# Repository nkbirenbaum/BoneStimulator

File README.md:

# bone-stimulator
Bone stimulator project w/ Saad Javeed

## PCB versions

+ bone_stim_v0  
  + Original constant bone stimulator circuit created by electronics shop  
  + Much larger and not designed to be implantable  
  + Potentiometer allowed for adjustment of stimulation current  
+ bone_stim_v1  
  + Nathan's edit of v0 circuit that makes circuit smaller and stimulation constant  
  + Used by Jawad Khalifeh in trial studies  
+ bone_stim_pulsed_v2  
  + Nathan's redesign for Saad Javeed based on literature ([Cho et al 2018](https://doi.org/10.1016/j.spinee.2018.12.011))  
  + Incorporates stimulator circuit controlled by ATTINY for pulsed stimulation  
  + Did not work on initial testing 4/12 and needed to be resized anyway (printed square from expressPCB)  
+ bone_stim_pulsed_v3  
  + Redesigned to have round edges and an incorporated schematic file  
  + Described below and should be used in future runs  

## Software versions

- Note: software versions do not correlate with PCB versions  
- bone_stim_v1  
  - Uses delay and delayMicroseconds (delay is not very accurate)  
- bone_stim_v2  
  - Uses if(millis() - time_now_ms > PULSE_PERIOD_MS) condition with time_now_ms as unsigned long  
- bone_stim_v3  
  - WORK IN PROGRESS  
  - Need to add button push and blinking funcitonality  
  - Need to sleep in between pulses  
  - Measure current draw if possible  

## Paper

+ "Effect of the type of electrical stimulation on spinal fusion in a rat posterolateral spinal fusion model" Pyung Goo Cho, MD, Gyu Yeol Ji, PhD, Yoon Ha, PhD, Hye Yeong Lee, Dong Ah Shin, MD, PhD. December 22, 2018 DOI: https://doi.org/10.1016/j.spinee.2018.12.011  
+ Link: [The Spine Journal](https://www.thespinejournalonline.com/article/S1529-9430(18)31320-2/fulltext)  
+   

# PCB design

- bone_stim_pulsed_v3 finalized by NKB 04/14/2022.  
- Gerber and drill files for ordering boards are available in the "bone_stim_pulsed_v3" folder.  

<sup>bone stim pulsed v3 PCB </sup>  

<sup>bone stim pulsed v3 schematic</sup>  

## Parts, datasheets, and schematics

+ Microcontroller
  + ATTINY13-10SSU ([DigiKey](https://www.digikey.com/en/products/detail/microchip-technology/ATTINY13V-10SSU/1008458) / [datasheet](https://ww1.microchip.com/downloads/en/DeviceDoc/2535S.pdf))  
  + ATTINY programming clip ([Amazon](https://www.amazon.com/Pomona-Electronics-5250-Plated-Spacing/dp/B00JJ4G13I/ref=sr_1_3?keywords=soic8+clip&qid=1645148900&sr=8-3))  
  + ATTINY pinout  

- Current source
  - LM334 ([DigiKey](https://www.digikey.com/en/products/detail/texas-instruments/LM334M/3701392) / [datasheet](https://www.ti.com/general/docs/suppproductinfo.tsp?distId=10&gotoUrl=https%3A%2F%2Fwww.ti.com%2Flit%2Fgpn%2Flm134))  

+ Pushbutton
  + EVQ-3PLA15 ([Digikey](https://www.digikey.com/en/products/detail/panasonic-electronic-components/EVQ-3PLA15/7561411?s=N4IgTCBcDaIAoEYxgCwGYBsBhAKgWgDkAREAXQF8g) / [datasheet](https://www3.panasonic.biz/ac/e_download/control/switch/light-touch/catalog/sw_lt_eng_49s.pdf))  

- LED
  - LS P476-Q1R2-1-0-20-R18-Z ([Digikey](https://www.digikey.com/en/products/detail/osram-opto-semiconductors-inc/LS-P476-Q1R2-1-0-20-R18-Z/7325513?s=N4IgjCBcoMxgnFUBjKAzAhgGwM4FMAaEAeygG1wYAmABhoHYQiBWADnpkaIDYwxmYTENyphuAFiFj2VKlKrUaiImAXjmzecwXd54kV3BVu8cYJUwaYeroC6RAA4AXKCADKTgE4BLAHYBzEABfFjMkEFRITFxCEnIQDmYJKTMaJKlWcRpuViFaOhMhHNYYcwSONKFMtLLTZnpJFTpLQXsQZ1cPHwDgnkzwyOj8IlJICjBqnJA2jsh3Lz9AkPBmOgH0bGG4sfAEbKE2VSKaBSL%2BZWFRC4l9IXolCCJ6MBO7-ho3jTuqcUfy56qNF%2BVVY%2BxmLjmXUWvRAAFo5NAIlAvABXWKjCiaWxBZYIig4AC2ABMAARYPCkzwUknTHjhbxE1ywl5-WYgIROACeDjwrgwOFQOKAA) / [datasheet](https://dammedia.osram.info/media/resource/hires/osram-dam-2493611/LS%20P476.pdf))  

+ Battery
  + CR-2450/H1AN ([Digikey](https://www.digikey.com/en/products/detail/panasonic-bsg/CR-2450-H1AN/2404067?s=N4IgTCBcDaIMYCcC0YAsBWADAegBIEYBBAORAF0BfIA) / [datasheet](https://b2b-api.panasonic.eu/file_stream/pids/fileversion/3648))
  + Search [Digikey](https://www.digikey.com/en/products/filter/batteries-non-rechargeable-primary/90?s=N4IgjCBcoMwExVAYygMwIYBsDOBTANCAPZQDaIM8YYMIhlc1ADHRVdaw9QgLqEAOAFyggAyoIBOASwB2AcxABferWggUkDDgLEy4AKwA2AJwAOCITD6A7KbiHWN-QBYmtS4abXr%2B1mEPOgQiEzt6h7uCGUaYRYHYwzsEgznampsZ%2BptYw1hmWxlZwEUWGdhYgcM5gRXkViV7FzuyslU3WDoSVAcbOLfr66bVwNsbW5cNZ1knDxgVDhjUs9ExwwxB8IEIi4tLySp0DiOpoWHiEJJDkMKYpTZw3N70bW5BikrIKyhVeGWoaWmddJcKAACABqnAAdHBwVDDLDnsJXgBVGRSQQAeVQAFlcOhsABXCS4fYgAC0CD%2BUEkBJ0F3Ivh4ii%2BlPISCIshBSFwmEwIIARuhBIJcBIAJ4gJlAA) for other batteries if out of stock (this search saves most of the relevant parameters but check pin spacing with PCB)  

- Capacitor
  - 1 µF, 0805 (2012 metric) packaging ([DigiKey](https://www.digikey.com/en/products/detail/kemet/C0805C105K5PAC7800/6097177?s=N4IgTCBcDaIMYAYAcCCscCMaDWqAOAhnAOwoIgC6AvkA))

+ Resistors
  + 1 kΩ, 0603 (1508 metric) packaging  
  + 200 Ω, 0603 (1508 metric) packaging  
  + 680 Ω, 0603 (1508 metric) packaging  
  + Sourced from [resistor sample book](https://www.amazon.com/Yobett-15pF-1uF-3725pcs-Resistor-Capacitor/dp/B00IN2314E/ref=sr_1_10?crid=UE07MO30ZN0Y&keywords=smd+resistor+variety+pack+0603&qid=1649957977&sprefix=smd+resistor+variety+pack+0603%2Caps%2C92&sr=8-10)

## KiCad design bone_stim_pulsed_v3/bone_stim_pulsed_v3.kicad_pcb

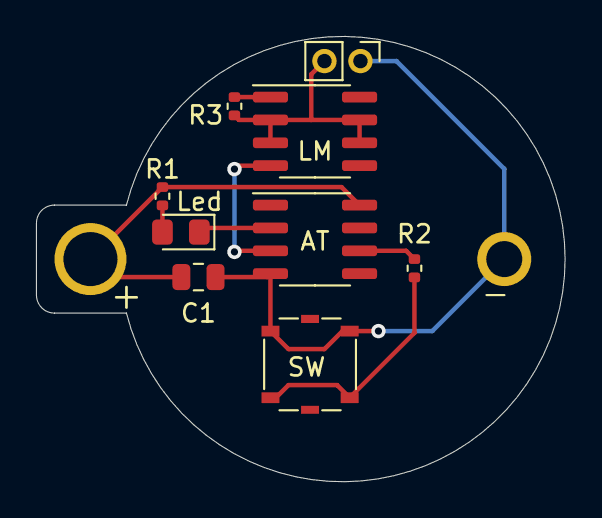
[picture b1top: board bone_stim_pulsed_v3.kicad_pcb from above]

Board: 2 copper layers, 29.4 x 24.7 mm, 10 parts (0 on the bottom side), 9 nets.

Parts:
 : 3.3V; BatteryHolder_Keystone_105_1x2430
 #2: Conn; PinHeader_1x02_P2.00mm_Vertical
AT: ATtiny13V-10SSU; SOIC-8_3.9x4.9mm_P1.27mm
C1: 1 μF; C_0805_2012Metric
LM: LM334M; SOIC-8_3.9x4.9mm_P1.27mm
Led: Red; LED_0805_2012Metric_Pad1.15x1.40mm_HandSolder
R1: 1 kΩ; R_0402_1005Metric
R2: 200 Ω; R_0402_1005Metric
R3: 680 Ω; R_0402_1005Metric
SW: SW_SPST_Panasonic_EVQPL_3PL_5PL_PT_A15

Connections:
+3V3: .1, AT.8, C1.1, R1.1
GND: .2, #2.1, AT.4, C1.2, SW.1
unnamed: AT.2, Led.1
unnamed: AT.3, LM.4
unnamed: AT.6, R2.2
unnamed: Led.2, R1.2
unnamed: LM.1, R3.2
unnamed: #2.2, LM.2, LM.3, LM.6, LM.7, R3.1
unnamed: R2.1, SW.2

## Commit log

2022-02-22 Add files via upload
    Files for settings up the Arduino Uno as an ISP and the ATTINY13 with a test blink sketch.
2022-04-14 Update README.md
    Updated parts list
2022-04-14 Update README.md
    Updated parts list and paper
2022-04-14 Update README.md
    Added circuit from paper
2022-04-14 Add files via upload
    design v2 (previously send to Saad via email)
2022-04-14 Add files via upload
    New design for fabrication 4/14/2022
2022-04-14 Add files via upload
    Old design Jawad Khalifeh was using that I designed a while ago.
2022-04-14 Add files via upload
    Old constant stim design from electronics shop
2022-04-14 Update README.md
    Added version descriptions.
2022-04-14 Update README.md
    added pcb and schematic
